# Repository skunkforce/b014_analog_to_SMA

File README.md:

# edgy_board number b014
This design is part of the [edgy board project](https://github.com/skunkforce/edgy_boards). It provides an SMA connector which can be connected to an analog connector. 

# getting started
This repository uses submodules. After cloning use the command 

```$ git submodule update --init --recursive```

to pull the submodules before opening the project with kicad.

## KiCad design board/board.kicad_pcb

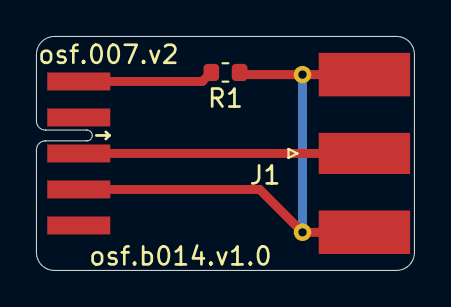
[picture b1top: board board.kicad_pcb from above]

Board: 2 copper layers, 21.0 x 13.0 mm, 3 parts (0 on the bottom side), 3 nets.

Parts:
J1: Conn_Coaxial; SMA_Molex_73251-1153_EdgeMount_Horizontal
J2: 007_ADC_2x2; on_edge_2x05_device
R1: d.n.p; R_0603_1608Metric

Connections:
GND: J2.1 (GND), R1.2
unnamed: J1.1 (In), J2.3 (ADC0)
unnamed: J1.2 (Ext), J2.4 (ADC1), R1.1

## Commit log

2023-02-28 initial
